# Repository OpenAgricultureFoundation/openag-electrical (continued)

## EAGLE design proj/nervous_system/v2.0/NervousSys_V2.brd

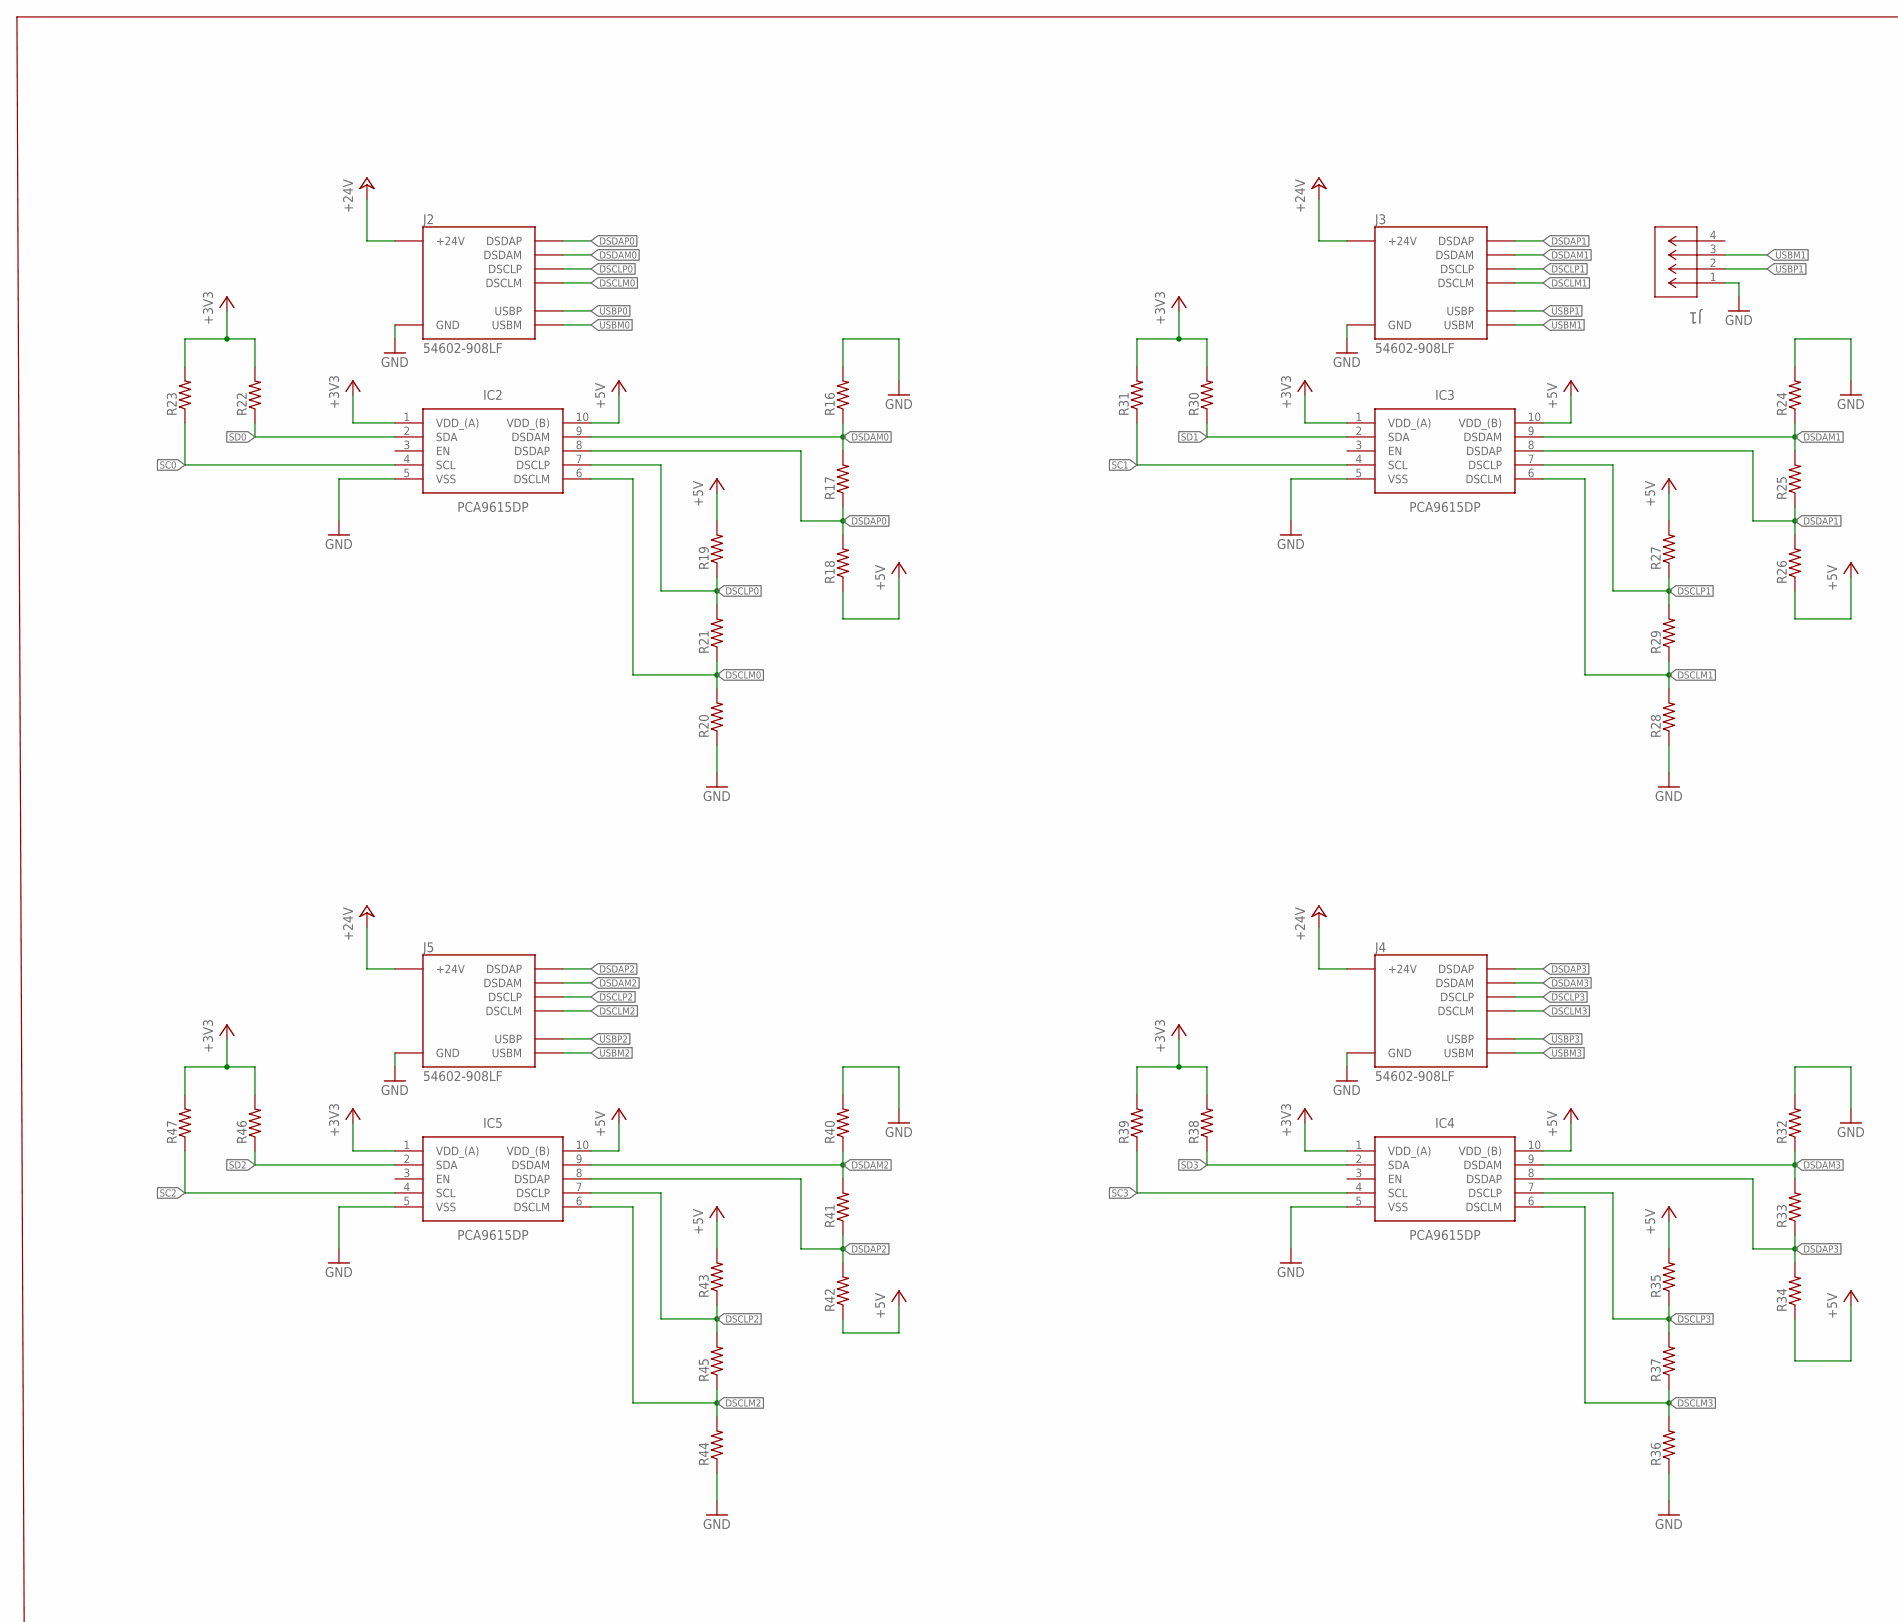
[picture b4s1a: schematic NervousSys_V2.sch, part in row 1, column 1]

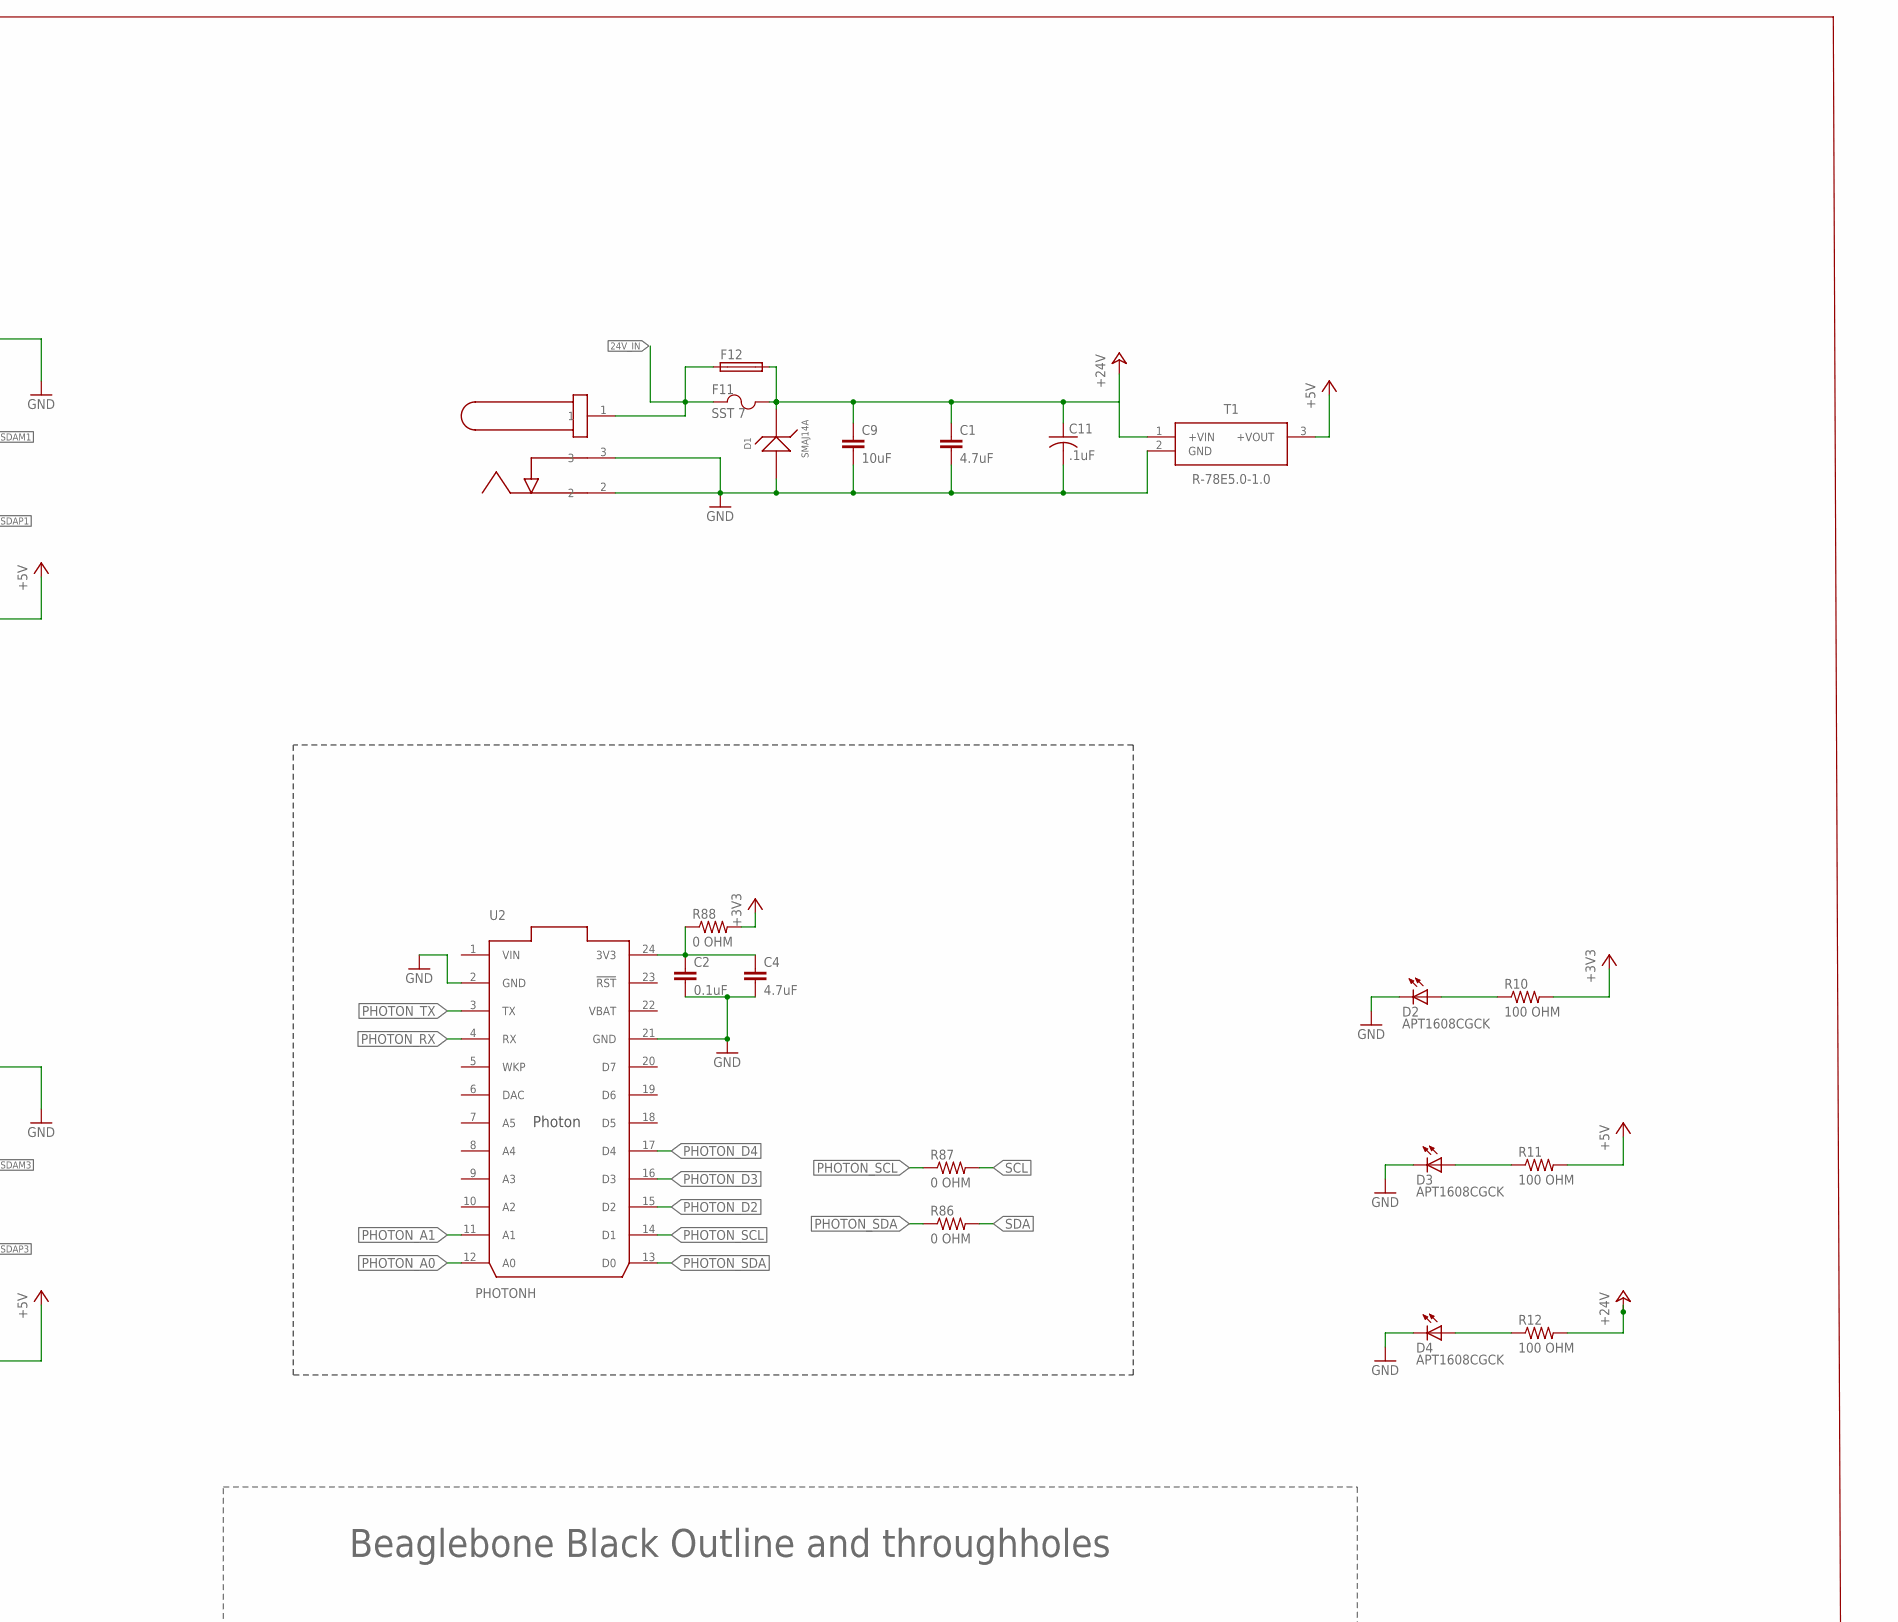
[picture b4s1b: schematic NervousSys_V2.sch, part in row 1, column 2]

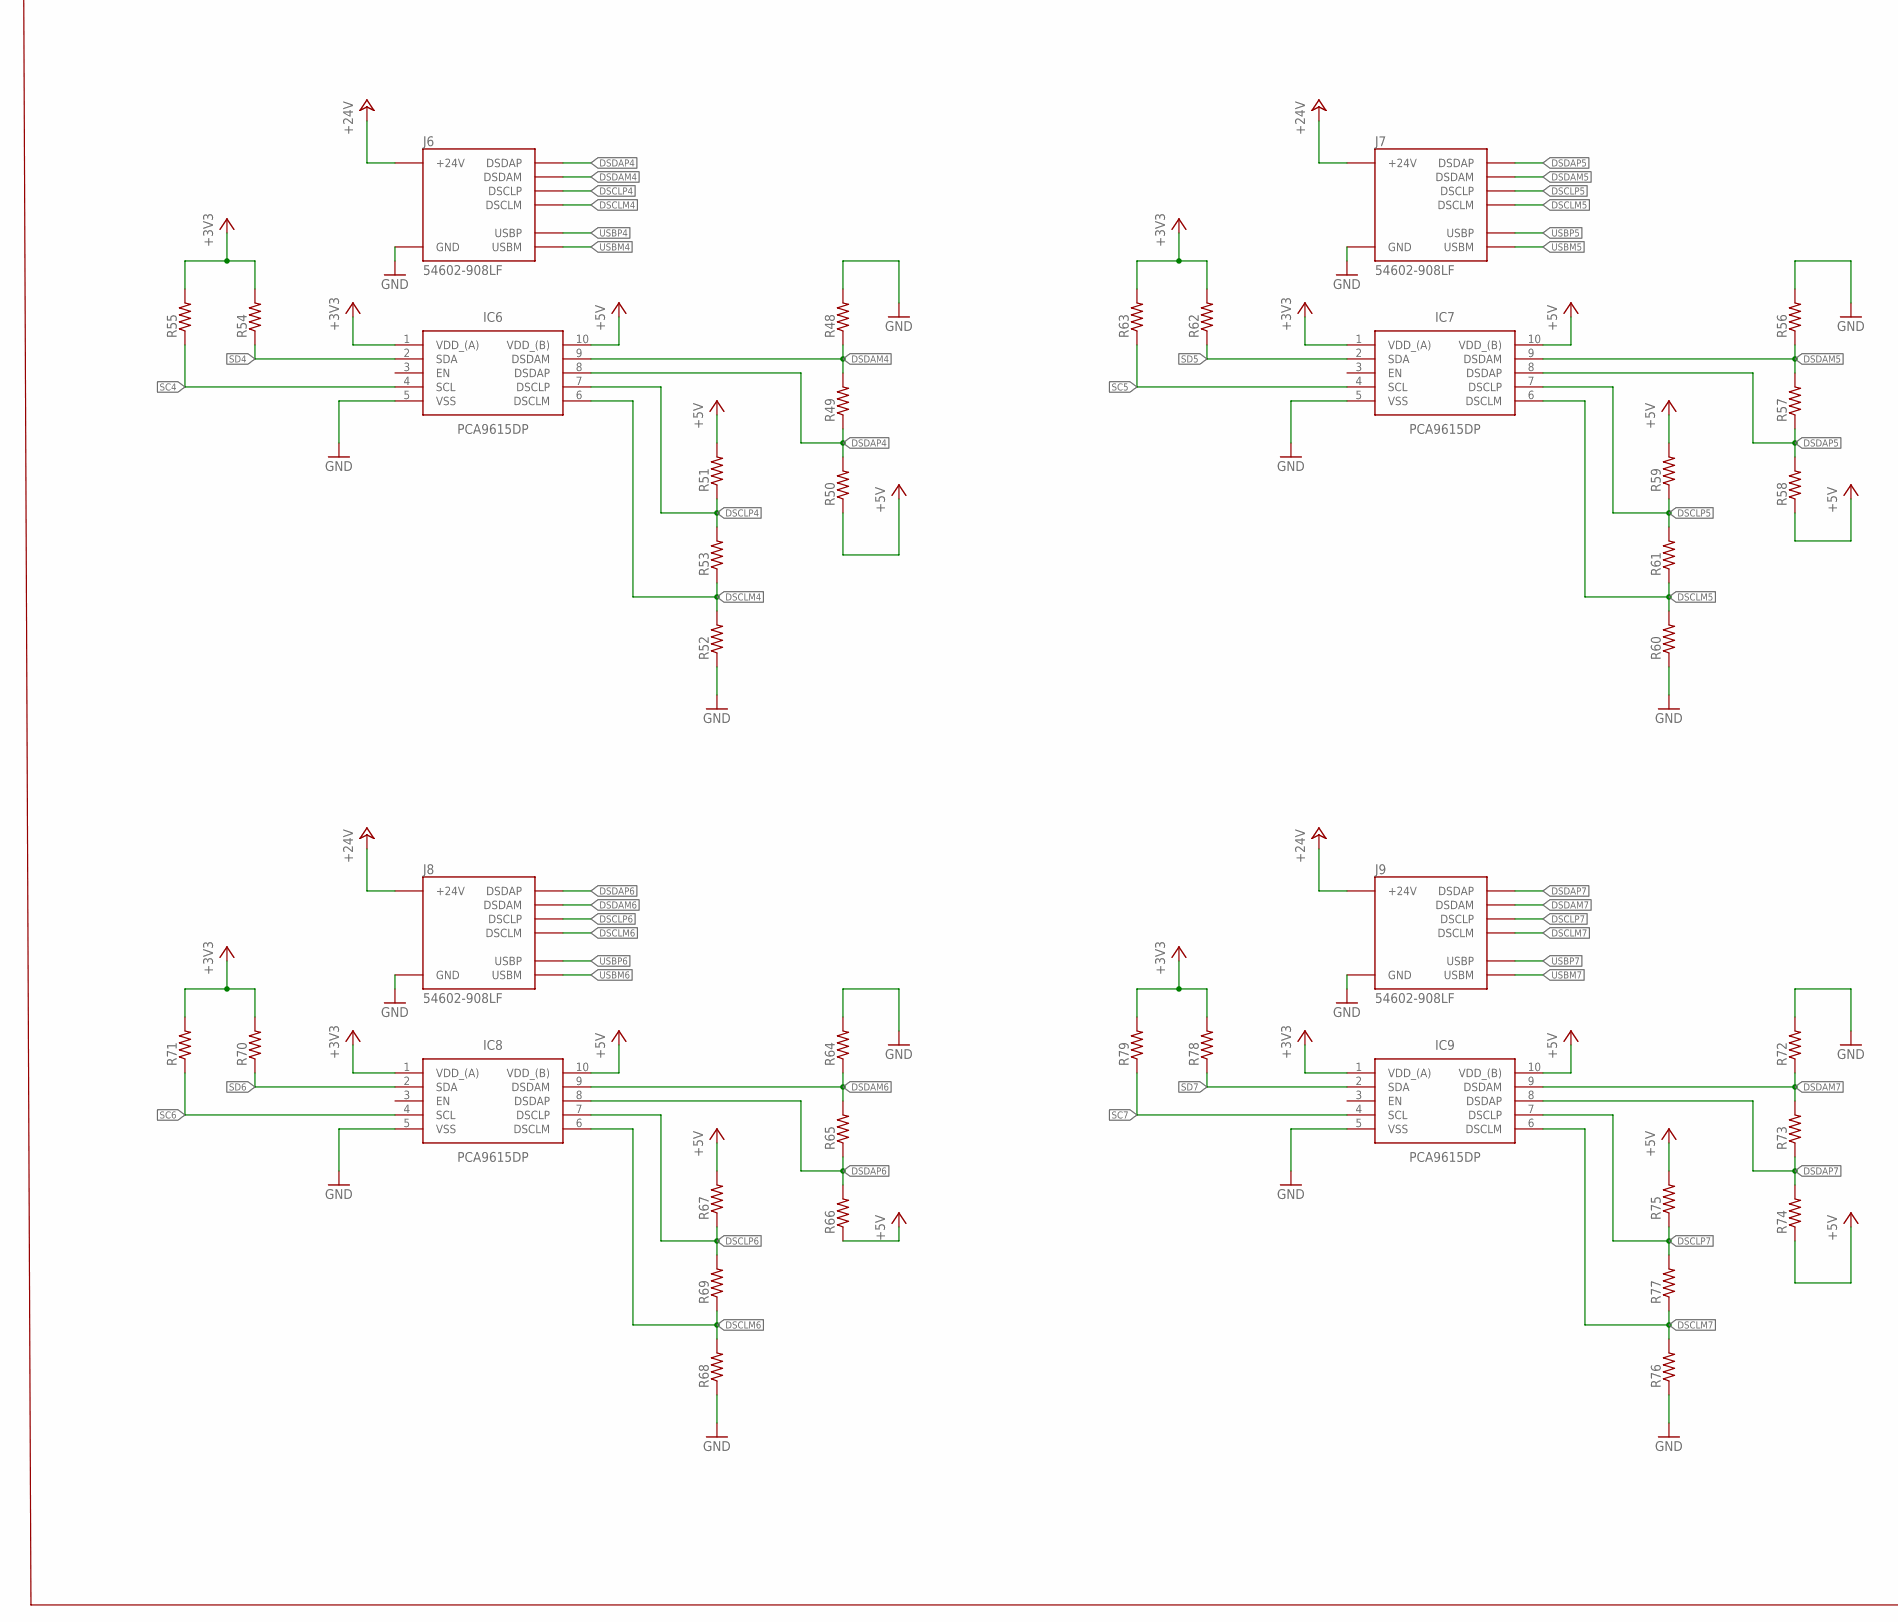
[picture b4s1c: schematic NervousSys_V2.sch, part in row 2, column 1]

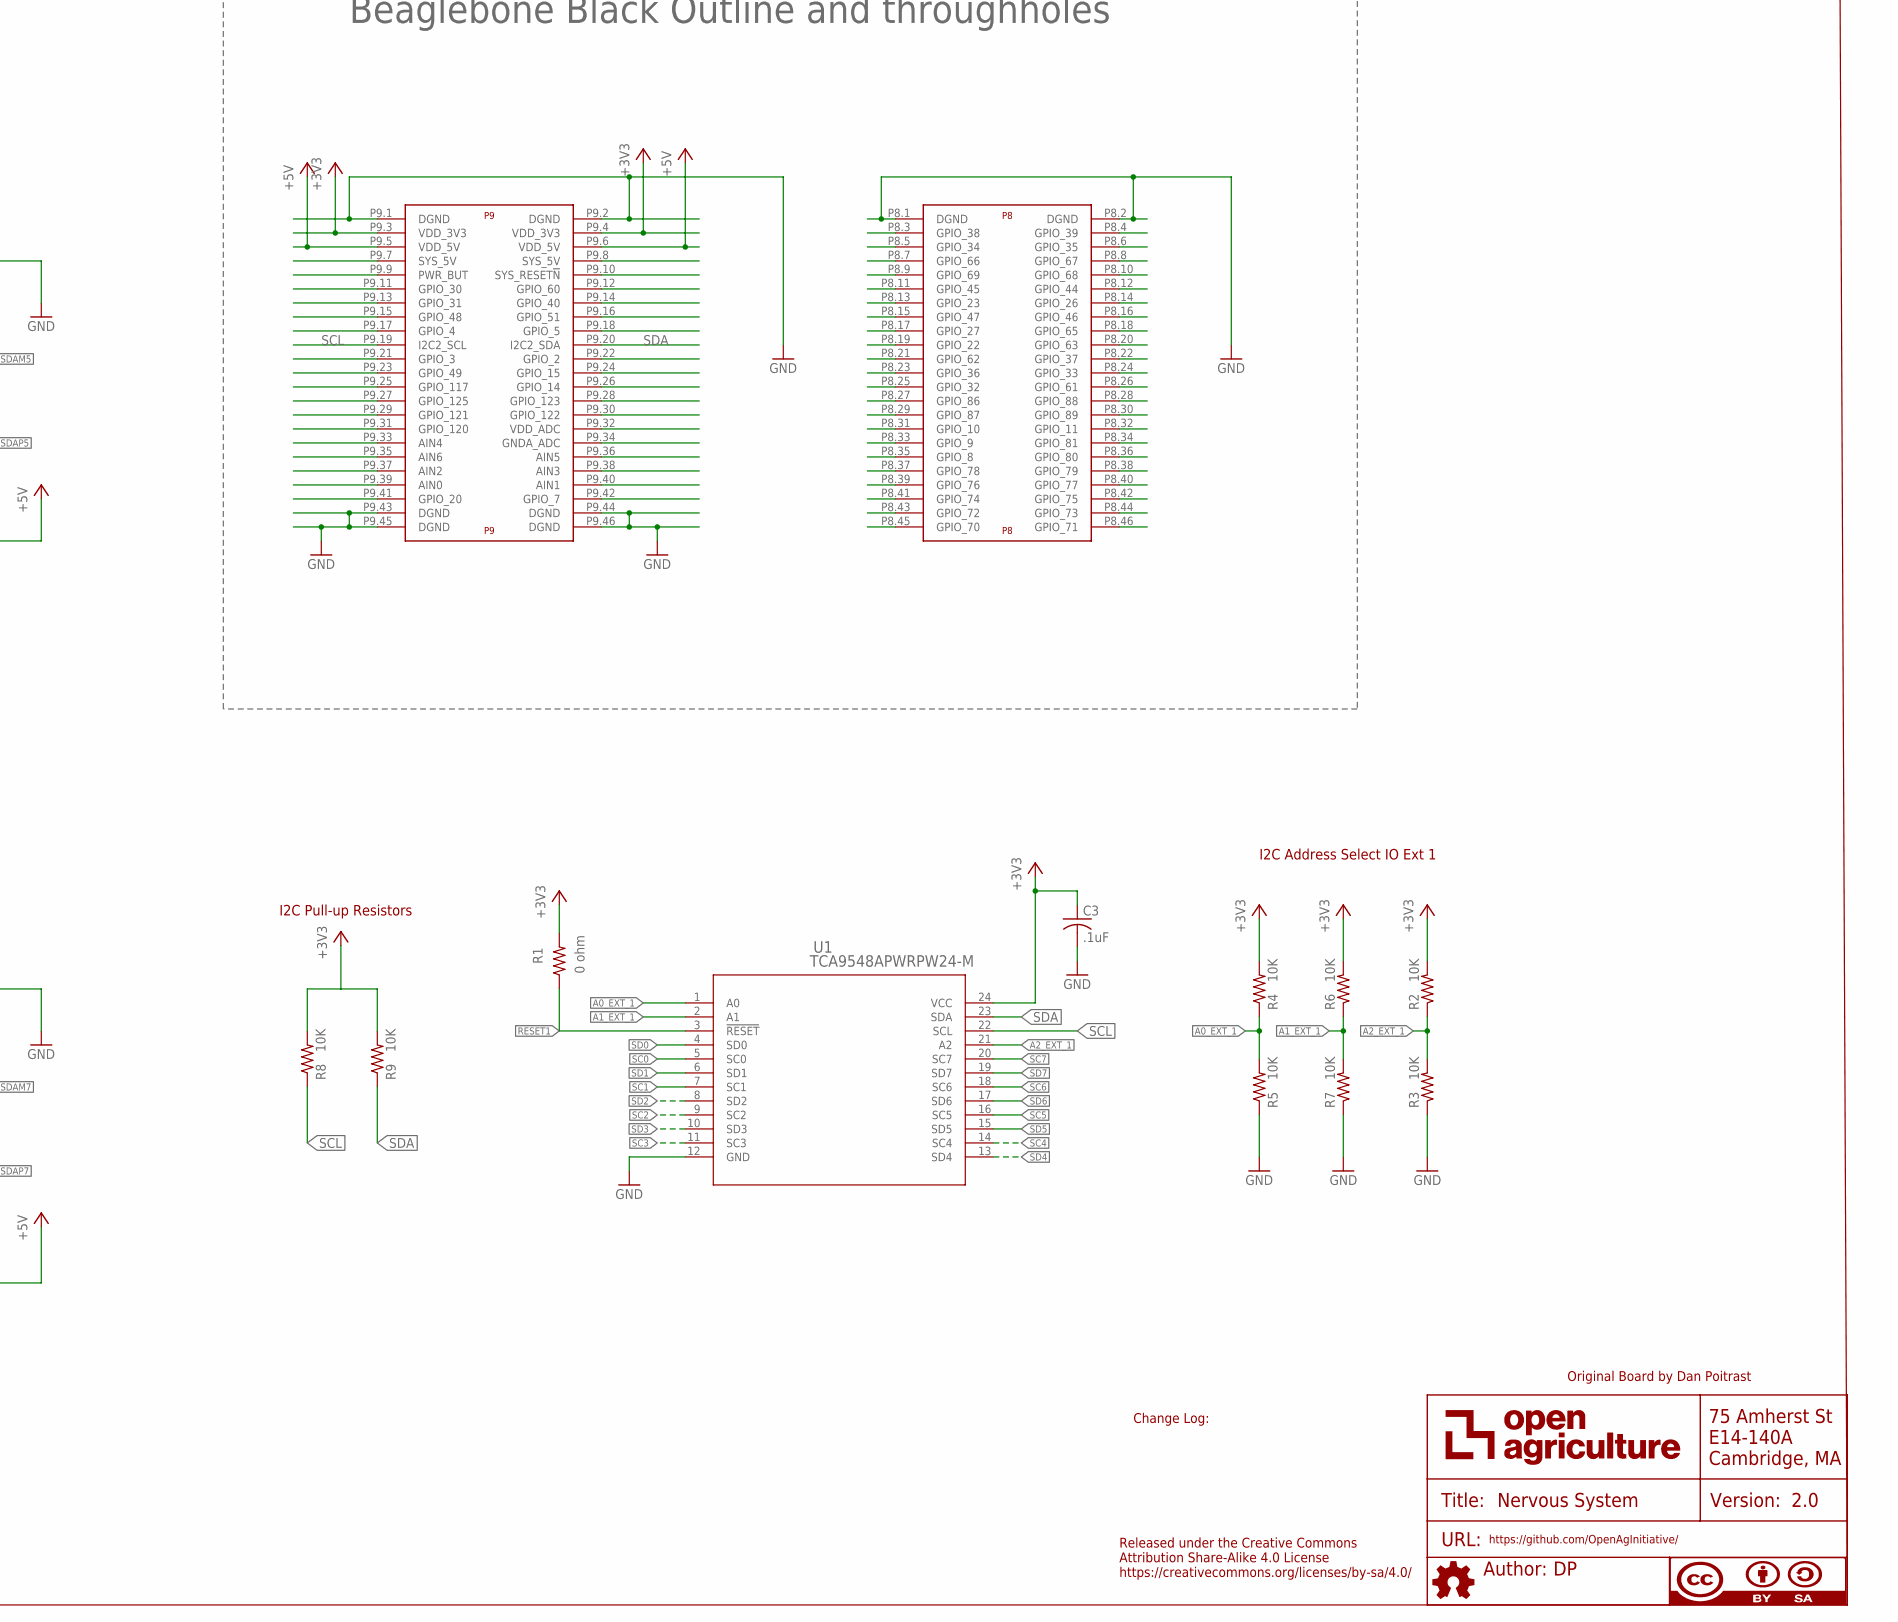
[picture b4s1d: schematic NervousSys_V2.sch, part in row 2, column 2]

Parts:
ATTRIBUTES: DOCFIELD
C1: 4.7uF; CAP_C1206
C2: 0.1uF; C0603
C3, C11: .1uF; C0603@1
C4: 4.7uF; C0805
C9: 10uF; C1206
D1: SMAJ14A; DO-214AC
D2, D3, D4: APT1608CGCK; CHIPLED_0603
F11: SST 7; SS
F12: GSH15
IC2, IC3, IC4, IC5, IC6, IC7, IC8, IC9: PCA9615DP; SOP50P490X110-10N
J1: 87583-2010BLF; CONN_USB-87583
J2, J3, J4, J5, J6, J7, J8, J9: 54602-908LF; OPENAG-V1-RJ45
R1: 0 ohm; R0603
R2, R3, R4, R5, R6, R7, R8, R9: 10K; 0603-RES
R10, R11, R12: 100 OHM; RC0603N
R16, R17, R18, R19, R20, R21, R22, R23, R24, R25, R26, R27, R28, R29, R30, R31, R32, R33, R34, R35, R36, R37, R38, R39, R40, R41, R42, R43, R44, R45, R46, R47, R48, R49, R50, R51, R52, R53, R54, R55, R56, R57, R58, R59, R60, R61, R62, R63, R64, R65, R66, R67, R68, R69, R70, R71, R72, R73, R74, R75, R76, R77, R78, R79: R-US_R0603; R0603
R86, R87, R88: 0 OHM; RC0603N
T1: R-78E5.0-1.0
U1: TCA9548APWRPW24-M; PW24-M
U2: PHOTONH; PHOTON
U$1: PJ-036AH
U$2: BEAGLE_BONE_BLACK_CAPE

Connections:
24V_IN: F11.1, F12.1, U$1.1
+3V3: C3.1, IC2.1 (VDD_(A)), IC3.1 (VDD_(A)), IC4.1 (VDD_(A)), IC5.1 (VDD_(A)), IC6.1 (VDD_(A)), IC7.1 (VDD_(A)), IC8.1 (VDD_(A)), IC9.1 (VDD_(A)), R1.2, R2.2, R4.2, R6.2, R8.2, R9.2, R10.2, R22.2, R23.2, R30.2, R31.2, R38.2, R39.2, R46.2, R47.2, R54.2, R55.2, R62.2, R63.2, R70.2, R71.2, R78.2, R79.2, R88.2, U1.24 (VCC), U$2.P9.3 (VDD_3V3), U$2.P9.4 (VDD_3V3)
+5V: IC2.10 (VDD_(B)), IC3.10 (VDD_(B)), IC4.10 (VDD_(B)), IC5.10 (VDD_(B)), IC6.10 (VDD_(B)), IC7.10 (VDD_(B)), IC8.10 (VDD_(B)), IC9.10 (VDD_(B)), R11.2, R18.1, R19.2, R26.1, R27.2, R34.1, R35.2, R42.1, R43.2, R50.1, R51.2, R58.1, R59.2, R66.1, R67.2, R74.1, R75.2, T1.3 (+VOUT), U$2.P9.5 (VDD_5V), U$2.P9.6 (VDD_5V)
+24V: C1.1, C9.1, C11.1, D1.C, F11.2, F12.2, J2.24V(6) (+24V), J3.24V(6) (+24V), J4.24V(6) (+24V), J5.24V(6) (+24V), J6.24V(6) (+24V), J7.24V(6) (+24V), J8.24V(6) (+24V), J9.24V(6) (+24V), R12.2, T1.1 (+VIN)
A0_EXT_1: R4.1, R5.2, U1.1 (A0)
A1_EXT_1: R6.1, R7.2, U1.2 (A1)
A2_EXT_1: R2.1, R3.2, U1.21 (A2)
DSCLM0: IC2.6 (DSCLM), J2.DSCLM(5) (DSCLM), R20.2, R21.1
DSCLM1: IC3.6 (DSCLM), J3.DSCLM(5) (DSCLM), R28.2, R29.1
DSCLM2: IC5.6 (DSCLM), J5.DSCLM(5) (DSCLM), R44.2, R45.1
DSCLM3: IC4.6 (DSCLM), J4.DSCLM(5) (DSCLM), R36.2, R37.1
DSCLM4: IC6.6 (DSCLM), J6.DSCLM(5) (DSCLM), R52.2, R53.1
DSCLM5: IC7.6 (DSCLM), J7.DSCLM(5) (DSCLM), R60.2, R61.1
DSCLM6: IC8.6 (DSCLM), J8.DSCLM(5) (DSCLM), R68.2, R69.1
DSCLM7: IC9.6 (DSCLM), J9.DSCLM(5) (DSCLM), R76.2, R77.1
DSCLP0: IC2.7 (DSCLP), J2.DSCLP(4) (DSCLP), R19.1, R21.2
DSCLP1: IC3.7 (DSCLP), J3.DSCLP(4) (DSCLP), R27.1, R29.2
DSCLP2: IC5.7 (DSCLP), J5.DSCLP(4) (DSCLP), R43.1, R45.2
DSCLP3: IC4.7 (DSCLP), J4.DSCLP(4) (DSCLP), R35.1, R37.2
DSCLP4: IC6.7 (DSCLP), J6.DSCLP(4) (DSCLP), R51.1, R53.2
DSCLP5: IC7.7 (DSCLP), J7.DSCLP(4) (DSCLP), R59.1, R61.2
DSCLP6: IC8.7 (DSCLP), J8.DSCLP(4) (DSCLP), R67.1, R69.2
DSCLP7: IC9.7 (DSCLP), J9.DSCLP(4) (DSCLP), R75.1, R77.2
DSDAM0: IC2.9 (DSDAM), J2.DSDAM(2) (DSDAM), R16.1, R17.2
DSDAM1: IC3.9 (DSDAM), J3.DSDAM(2) (DSDAM), R24.1, R25.2
DSDAM2: IC5.9 (DSDAM), J5.DSDAM(2) (DSDAM), R40.1, R41.2
DSDAM3: IC4.9 (DSDAM), J4.DSDAM(2) (DSDAM), R32.1, R33.2
DSDAM4: IC6.9 (DSDAM), J6.DSDAM(2) (DSDAM), R48.1, R49.2
DSDAM5: IC7.9 (DSDAM), J7.DSDAM(2) (DSDAM), R56.1, R57.2
DSDAM6: IC8.9 (DSDAM), J8.DSDAM(2) (DSDAM), R64.1, R65.2
DSDAM7: IC9.9 (DSDAM), J9.DSDAM(2) (DSDAM), R72.1, R73.2
DSDAP0: IC2.8 (DSDAP), J2.DSDAP(1) (DSDAP), R17.1, R18.2
DSDAP1: IC3.8 (DSDAP), J3.DSDAP(1) (DSDAP), R25.1, R26.2
DSDAP2: IC5.8 (DSDAP), J5.DSDAP(1) (DSDAP), R41.1, R42.2
DSDAP3: IC4.8 (DSDAP), J4.DSDAP(1) (DSDAP), R33.1, R34.2
DSDAP4: IC6.8 (DSDAP), J6.DSDAP(1) (DSDAP), R49.1, R50.2
DSDAP5: IC7.8 (DSDAP), J7.DSDAP(1) (DSDAP), R57.1, R58.2
DSDAP6: IC8.8 (DSDAP), J8.DSDAP(1) (DSDAP), R65.1, R66.2
DSDAP7: IC9.8 (DSDAP), J9.DSDAP(1) (DSDAP), R73.1, R74.2
GND: C1.2, C2.2, C3.2, C4.2, C9.2, C11.2, D1.A, D2.C, D3.C, D4.C, IC2.5 (VSS), IC3.5 (VSS), IC4.5 (VSS), IC5.5 (VSS), IC6.5 (VSS), IC7.5 (VSS), IC8.5 (VSS), IC9.5 (VSS), J1.1, J2.GND(3) (GND), J3.GND(3) (GND), J4.GND(3) (GND), J5.GND(3) (GND), J6.GND(3) (GND), J7.GND(3) (GND), J8.GND(3) (GND), J9.GND(3) (GND), R3.1, R5.1, R7.1, R16.2, R20.1, R24.2, R28.1, R32.2, R36.1, R40.2, R44.1, R48.2, R52.1, R56.2, R60.1, R64.2, R68.1, R72.2, R76.1, T1.2 (GND), U1.12 (GND), U2.2 (GND), U2.21 (GND), U$1.2, U$1.3, U$2.P8.1 (DGND), U$2.P8.2 (DGND), U$2.P9.1 (DGND), U$2.P9.2 (DGND), U$2.P9.43 (DGND), U$2.P9.44 (DGND), U$2.P9.45 (DGND), U$2.P9.46 (DGND)
unnamed: D3.A, R11.1
unnamed: D4.A, R12.1
unnamed: C2.1, C4.1, R88.1, U2.24 (3V3)
unnamed: D2.A, R10.1
PHOTON_A0: U2.12 (A0)
PHOTON_A1: U2.11 (A1)
PHOTON_D2: U2.15 (D2)
PHOTON_D3: U2.16 (D3)
PHOTON_D4: U2.17 (D4)
PHOTON_RX: U2.4 (RX)
PHOTON_SCL: R87.1, U2.14 (D1)
PHOTON_SDA: R86.1, U2.13 (D0)
PHOTON_TX: U2.3 (TX)
RESET1: R1.1, U1.3 (!RESET)
SC0: IC2.4 (SCL), R23.1, U1.5 (SC0)
SC1: IC3.4 (SCL), R31.1, U1.7 (SC1)
SC2: IC5.4 (SCL), R47.1, U1.9 (SC2)
SC3: IC4.4 (SCL), R39.1, U1.11 (SC3)
SC4: IC6.4 (SCL), R55.1, U1.14 (SC4)
SC5: IC7.4 (SCL), R63.1, U1.16 (SC5)
SC6: IC8.4 (SCL), R71.1, U1.18 (SC6)
SC7: IC9.4 (SCL), R79.1, U1.20 (SC7)
SCL: R8.1, R87.2, U1.22 (SCL), U$2.P9.19 (I2C2_SCL)
SD0: IC2.2 (SDA), R22.1, U1.4 (SD0)
SD1: IC3.2 (SDA), R30.1, U1.6 (SD1)
SD2: IC5.2 (SDA), R46.1, U1.8 (SD2)
SD3: IC4.2 (SDA), R38.1, U1.10 (SD3)
SD4: IC6.2 (SDA), R54.1, U1.13 (SD4)
SD5: IC7.2 (SDA), R62.1, U1.15 (SD5)
SD6: IC8.2 (SDA), R70.1, U1.17 (SD6)
SD7: IC9.2 (SDA), R78.1, U1.19 (SD7)
SDA: R9.1, R86.2, U1.23 (SDA), U$2.P9.20 (I2C2_SDA)
USBM0: J2.USBM(8) (USBM)
USBM1: J1.3, J3.USBM(8) (USBM)
USBM2: J5.USBM(8) (USBM)
USBM3: J4.USBM(8) (USBM)
USBM4: J6.USBM(8) (USBM)
USBM5: J7.USBM(8) (USBM)
USBM6: J8.USBM(8) (USBM)
USBM7: J9.USBM(8) (USBM)
USBP0: J2.USBP(7) (USBP)
USBP1: J1.2, J3.USBP(7) (USBP)
USBP2: J5.USBP(7) (USBP)
USBP3: J4.USBP(7) (USBP)
USBP4: J6.USBP(7) (USBP)
USBP5: J7.USBP(7) (USBP)
USBP6: J8.USBP(7) (USBP)
USBP7: J9.USBP(7) (USBP)
VBAT: U2.22 (VBAT)
VIN: U2.1 (VIN)

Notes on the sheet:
Original Board by Dan Poitrast
Change Log:
I2C Pull-up Resistors
Released under the Creative Commons Attribution Share-Alike 4.0 License https://creativecommons.org/licenses/by-sa/4.0/
I2C Address Select IO Ext 1
Beaglebone Black Outline and throughholes

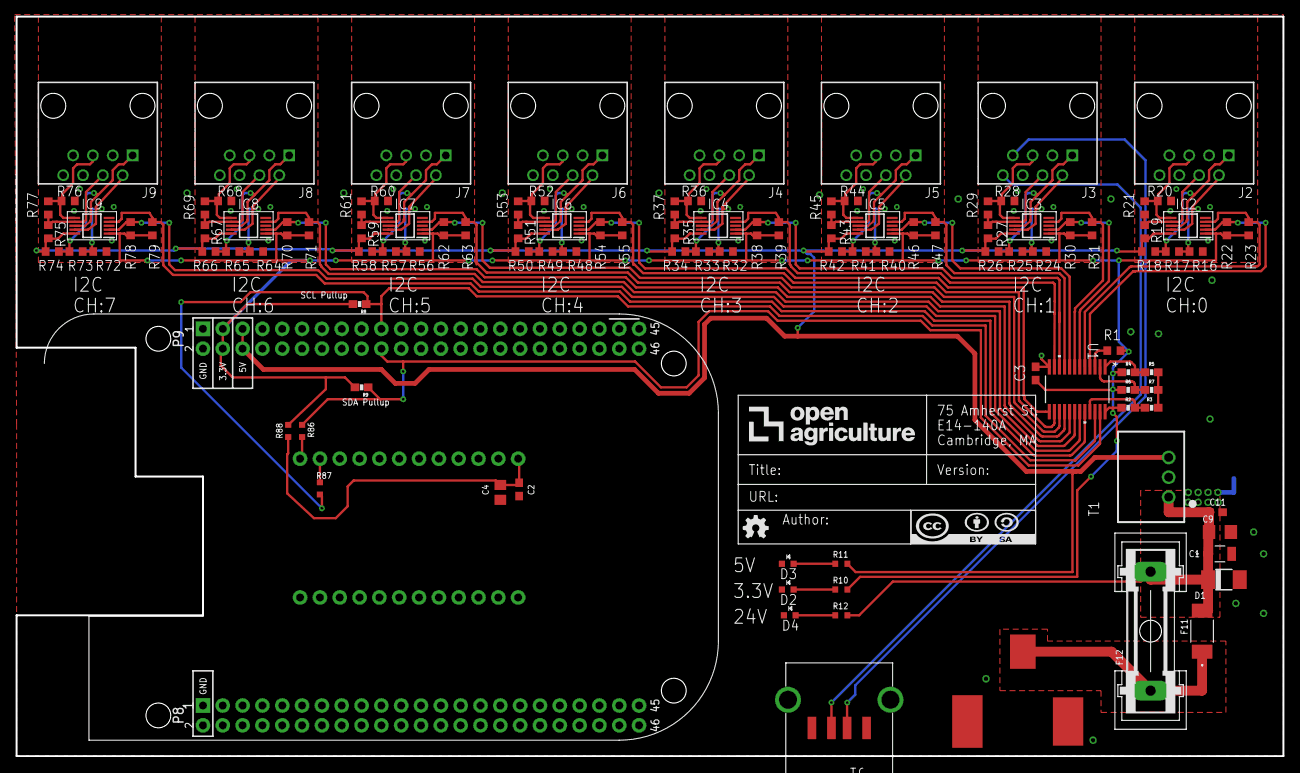
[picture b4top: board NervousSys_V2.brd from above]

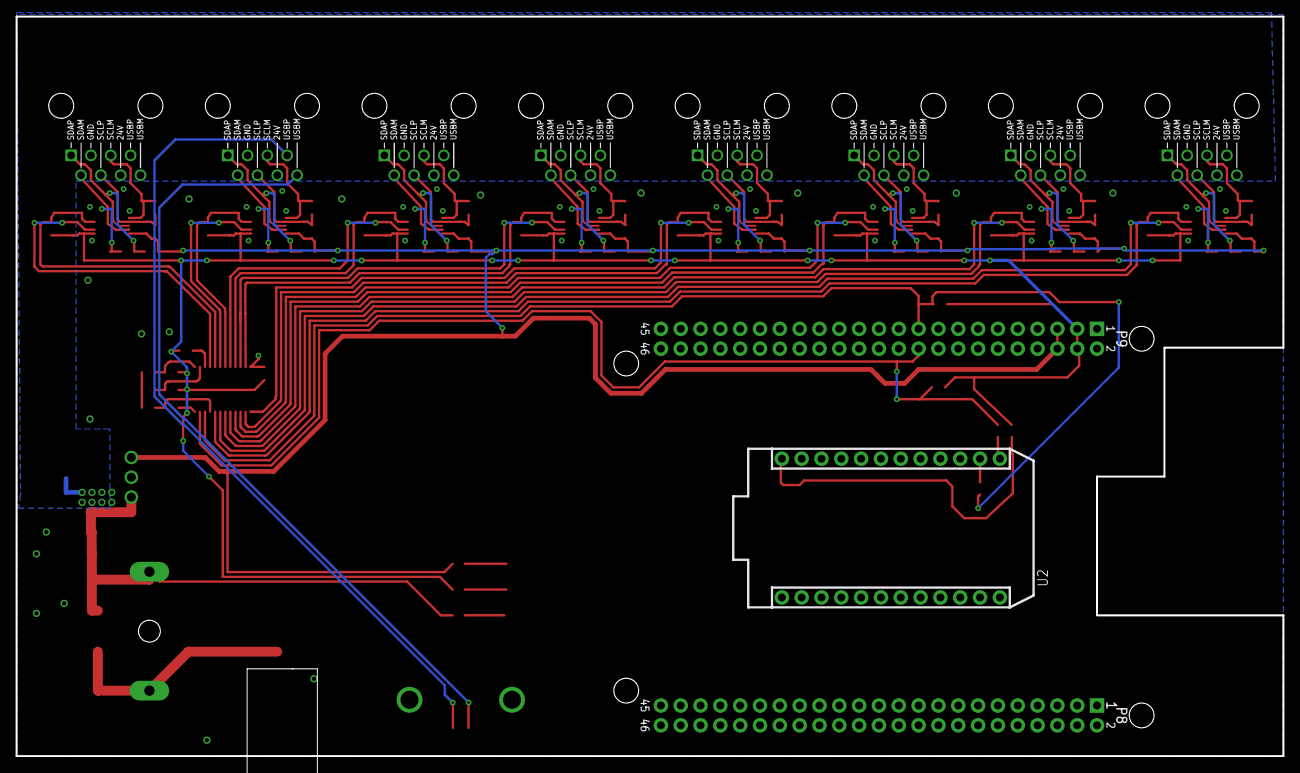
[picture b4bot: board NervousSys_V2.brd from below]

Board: 2 copper layers, 162.3 x 94.7 mm, 114 parts (2 on the bottom side), 67 nets.

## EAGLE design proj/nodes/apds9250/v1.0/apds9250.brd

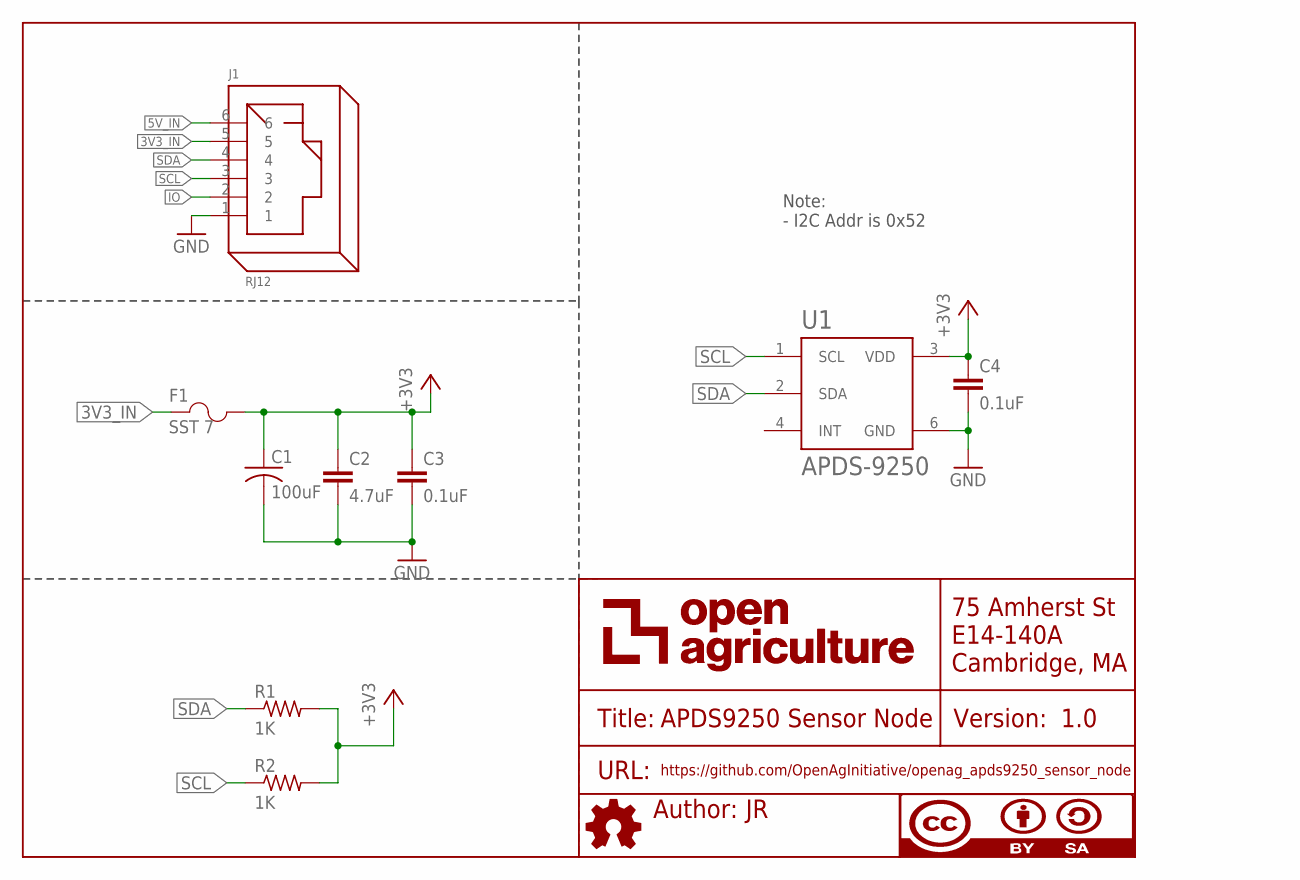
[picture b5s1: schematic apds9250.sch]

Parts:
C1: 100uF; EEE-1HA101UP
C2: 4.7uF; C0805
C3, C4: 0.1uF; C0603
F1: SST 7; SS
FRAME1: DOCFIELD
J1: RJ12
R1, R2: 1K; RC0603N
U1: APDS-9250

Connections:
3V3_IN: F1.1, J1.5
5V_IN: J1.6
+3V3: C1.+ (1(+)), C2.1, C3.1, C4.1, F1.2, R1.2, R2.2, U1.3 (VDD)
GND: C1.- (2(-)), C2.2, C3.2, C4.2, J1.1, U1.6 (GND)
IO: J1.2
SCL: J1.3, R2.1, U1.1 (SCL)
SDA: J1.4, R1.1, U1.2 (SDA)

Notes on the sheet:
Note: - I2C Addr is 0x52

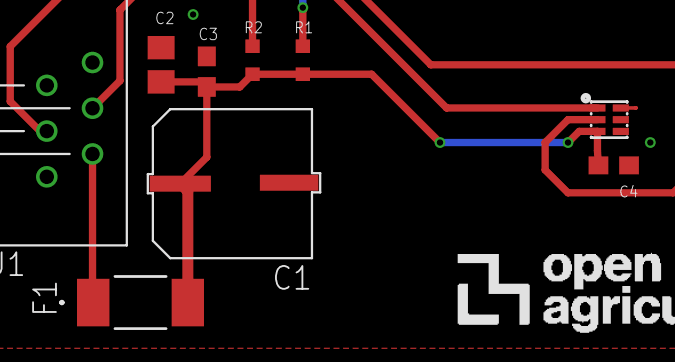
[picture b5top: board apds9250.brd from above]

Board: 2 copper layers, 11 parts (1 on the bottom side), 5 nets.

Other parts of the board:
U$2: OPENAG-LOGO-750-MIL

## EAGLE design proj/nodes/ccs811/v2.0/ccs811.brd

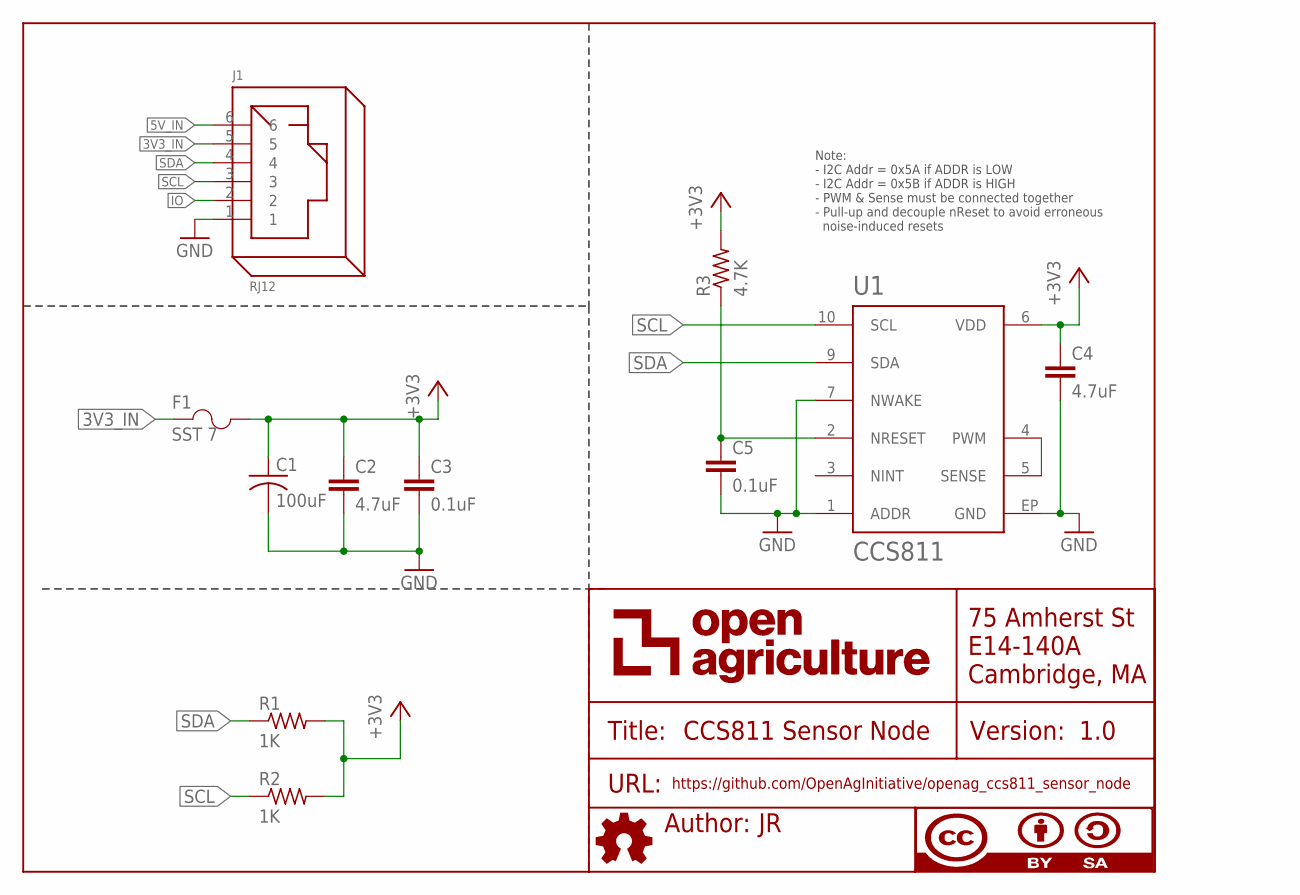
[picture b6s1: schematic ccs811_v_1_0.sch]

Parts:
C1: 100uF; EEE-1HA101UP
C2, C4: 4.7uF; C0805
C3, C5: 0.1uF; C0603
F1: SST 7; SS
FRAME1: DOCFIELD
J1: RJ12
R1, R2: 1K; RC0603N
R3: 4.7K; R1206
U1: CCS811

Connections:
3V3_IN: F1.1, J1.5
5V_IN: J1.6
+3V3: C1.+ (1(+)), C2.1, C3.1, C4.1, F1.2, R1.2, R2.2, R3.2, U1.6 (VDD)
GND: C1.- (2(-)), C2.2, C3.2, C4.2, C5.2, J1.1, U1.1 (ADDR), U1.7 (NWAKE), U1.EP (GND)
IO: J1.2
unnamed: U1.4 (PWM), U1.5 (SENSE)
unnamed: C5.1, R3.1, U1.2 (NRESET)
SCL: J1.3, R2.1, U1.10 (SCL)
SDA: J1.4, R1.1, U1.9 (SDA)

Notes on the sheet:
Note: - I2C Addr = 0x5A if ADDR is LOW - I2C Addr = 0x5B if ADDR is HIGH - PWM & Sense must be connected together - Pull-up and decouple nReset to avoid erroneous noise-induced resets

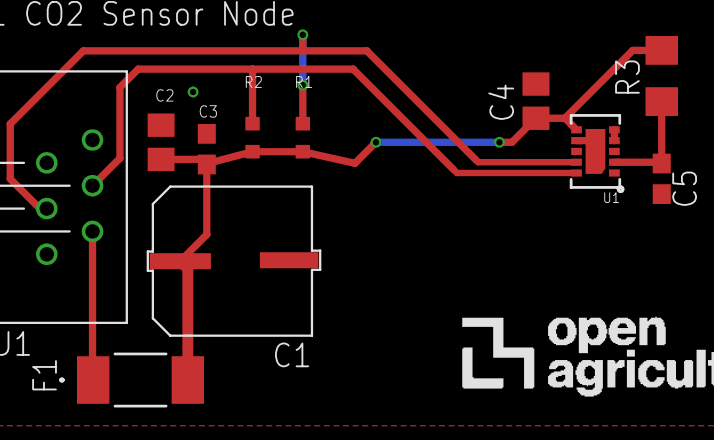
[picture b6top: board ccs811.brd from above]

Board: 2 copper layers, 13 parts (1 on the bottom side), 7 nets.

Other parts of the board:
U$1: OPENAG-LOGO-750-MIL
